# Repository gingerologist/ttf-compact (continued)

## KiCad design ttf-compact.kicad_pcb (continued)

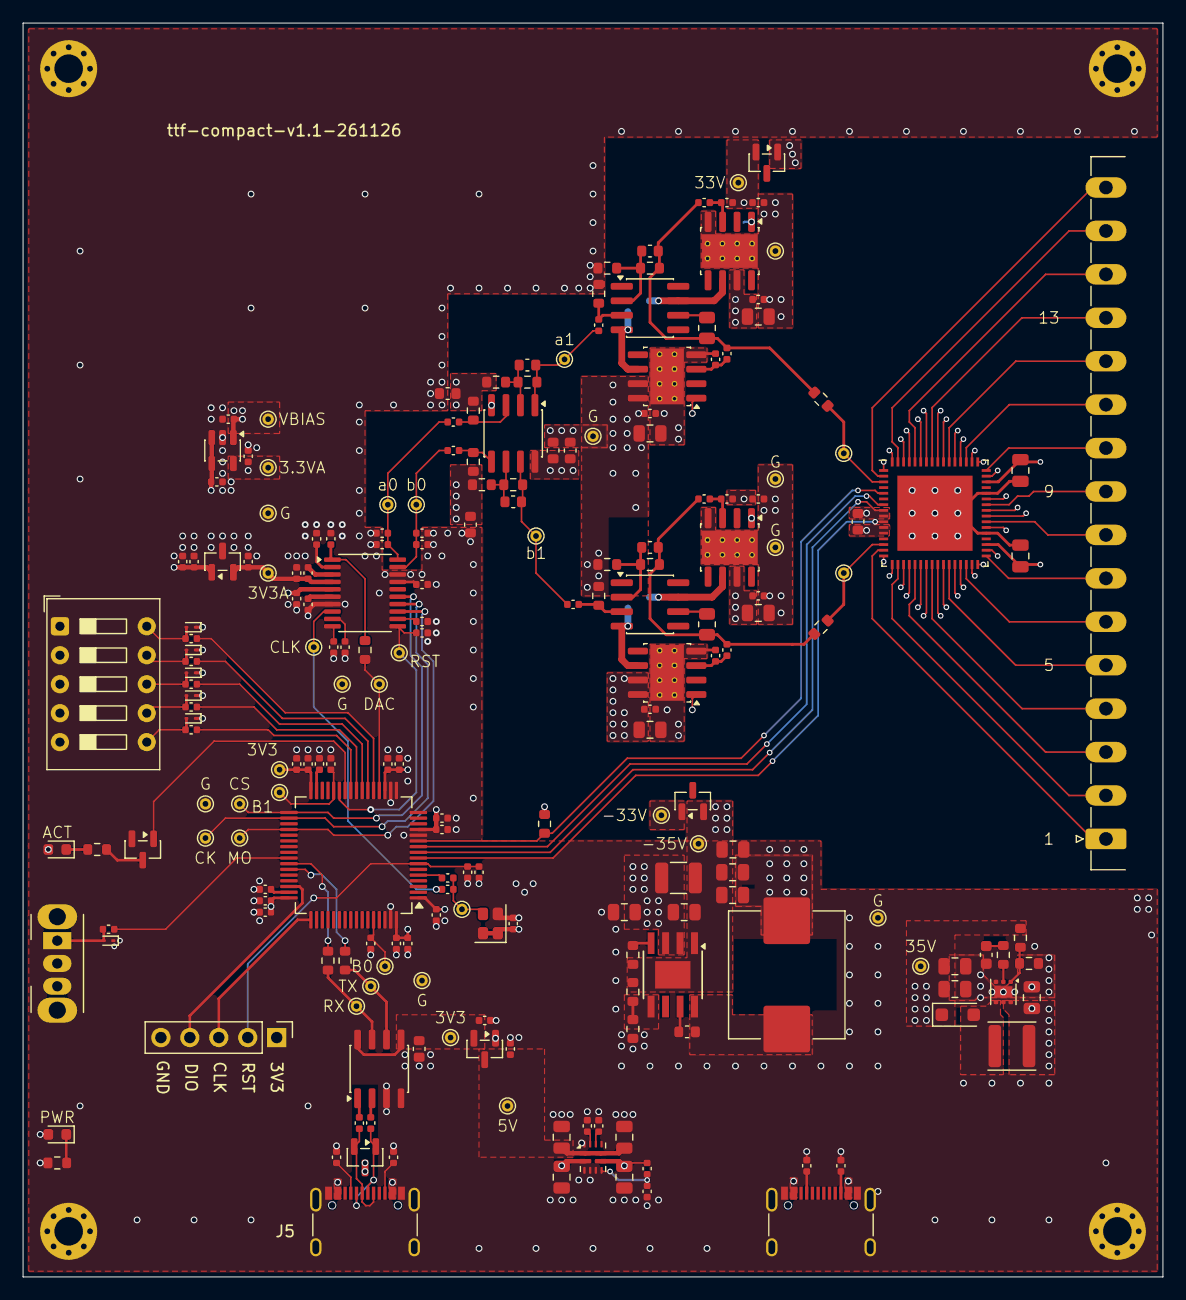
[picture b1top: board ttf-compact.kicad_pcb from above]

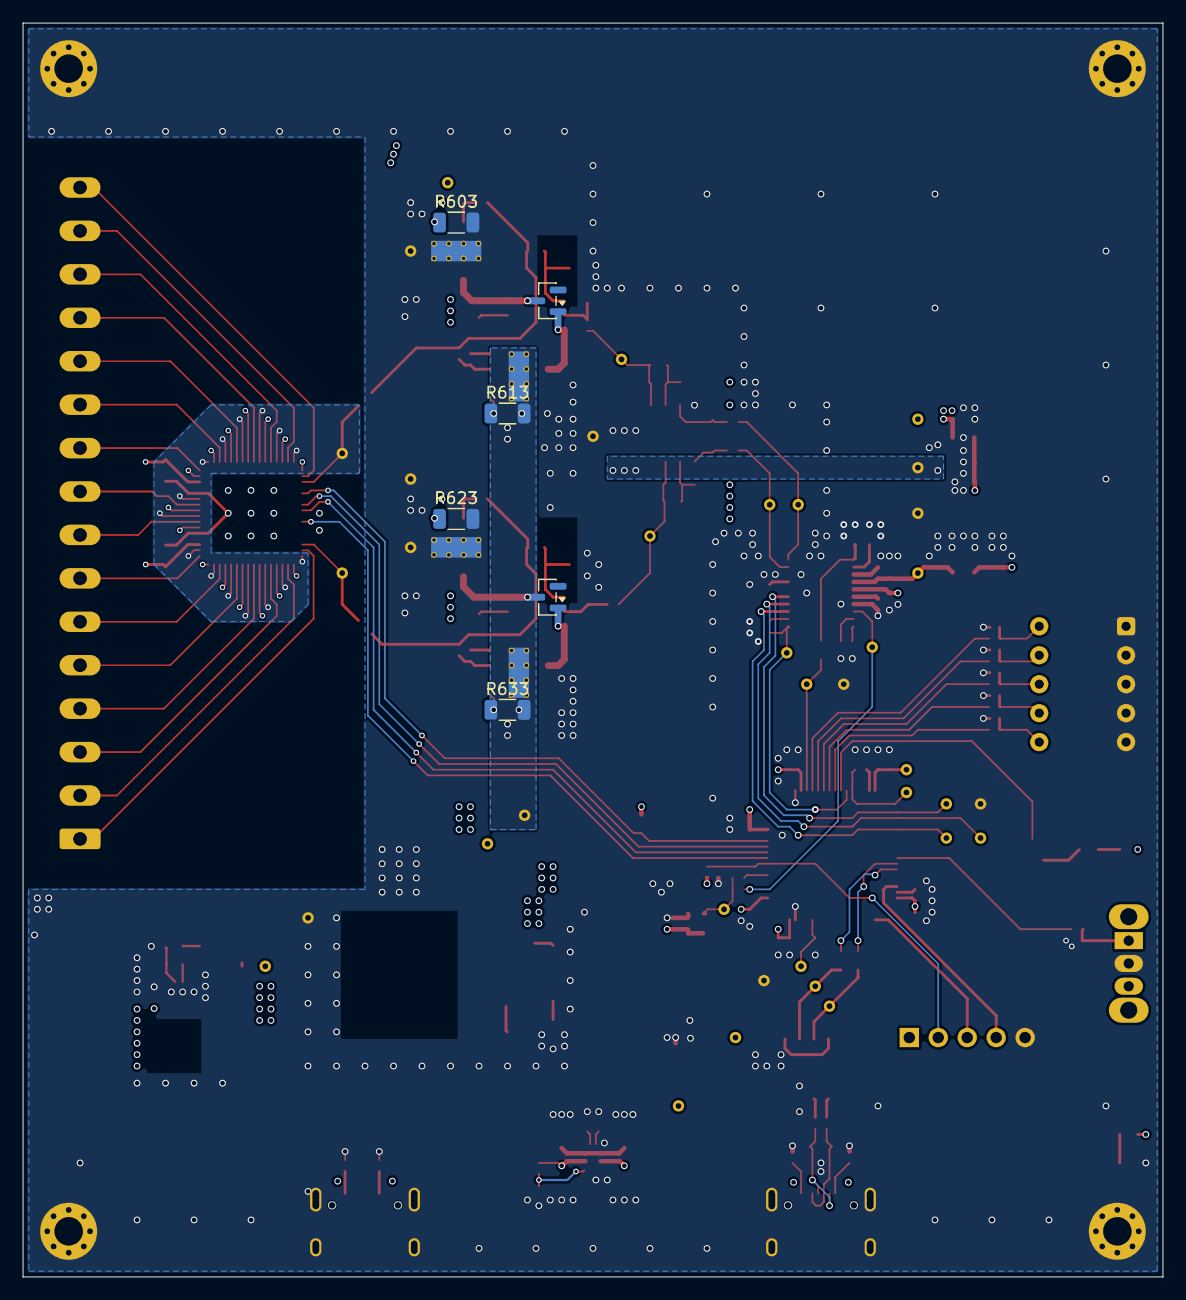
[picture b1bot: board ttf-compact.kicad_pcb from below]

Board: 4 copper layers, 100.0 x 110.0 mm, 221 parts (6 on the bottom side), 124 nets.

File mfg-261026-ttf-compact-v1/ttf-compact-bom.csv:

"Comment","Description","Designator","Footprint","Quantity","Supplier Part"
"1u,10%,25V","Unpolarized capacitor","C1,C15,C32,C33,C55,C650,C652,C660,C662,C985,C986,C987","0402","12","C52923"
"100n,10%,50V","Unpolarized capacitor","C2,C18,C602,C603,C612,C622,C623,C632","0402","8","C307331"
"10n,10%,50V","Unpolarized capacitor","C3,C4","0402","2","C15195"
"18p,±5%,50V","Unpolarized capacitor","C5,C10","0402","2","C1549"
"100n,10%,16V","Unpolarized capacitor","C6,C9,C11,C36,C37,C38,C50,C51,C52,C53,C54,C60","0402","12","C1525"
"2.2u,20%,6.3V","Unpolarized capacitor","C7,C8,C56,C57,C58,C59","0402","6","C12530"
"100n,10%,50V","Unpolarized capacitor","C31,C405,C667","0603","3","C14663"
"10u,10%,50V","Unpolarized capacitor","C301,C304,C400,C403,C404,C601,C611,C621,C631,C700,C701,C702,C703,C704","0805","14","C440198"
"15n,10%,50V","Unpolarized capacitor","C302","0603","1","C5137641"
"2.2u,10%,50V","Unpolarized capacitor","C303","0805","1","C377773"
"10u,10%,100V","10u, 100V Cap","C401","1210","1","C5156756"
"100n,10%,100V","Unpolarized capacitor","C402,C503,C504","0805","3","C28233"
"1u,10%,50V","Unpolarized capacitor","C501","0603","1","C15849"
"10p,5%,50V","Unpolarized capacitor","C651,C653,C661,C663","0603","4","C1634"
"2.2u,10%,16V","Unpolarized capacitor","C654,C664,C668","0603","3","C23630"
"GREEN","Green LED","D1,D7","0603","2","C84267"
"3.3V,15p","3.3V ESD","D2,D3,D4,D5,D6,D8","SOD-923","6","C96512"
"BAV99,215","Dual Switching Diode","D9,D10","SOT-23","2","C2500"
"100V,2A","100V 2A Schottky","D301","SOD-123FL","1","C511868"
"1x16P,3.81mm","Terminal Block","J1","RA,P=3.81mm","1","C127850"
"USB_C_U262-161N-4BVC11","USB-C 2.0 Receptacle","J5,J999","USBC20_16P","2","C319148"
"12uH,20%,1.7A","Inductor","L301","SMD,4x4mm","1","C96892"
"68uH,20%,3A","Power Inductor","L401","SMD,11x10mm","1","C408492"
"DTC143ZCA","Digital Transistor","Q1","SOT-23","1","C15236"
"10R,1%","Resistor","R1,R2","0603","2","C22859"
"10k,1%","Resistor","R4,R6,R7,R8,R10,R11,R18","0402","7","C25744"
"6.8k,1%","Resistor","R5","0603","1","C23212"
"33R,1%","Resistor","R9,R17","0402","2","C25105"
"220R,0.1%","Resistor","R13,R14","0402","2","C853134"
"22R,1%","Resistor","R31,R32","0402","2","C25092"
"5.1k,1%","Resistor","R33,R35,R998,R999","0402","4","C25905"
"0R,1%","Resistor","R36,R37","0603","2","C21189"
"100R,1%","Resistor","R40,R41,R42,R43,R44,R45","0402","6","C25076"
"10k,1%","Resistor","R93,R94,R403,R655,R665","0603","5","C25804"
"86.6k,1%","Resistor","R301","0603","1","C3000725"
"287k,1%","Resistor","R302","0603","1","C5159700"
"10.5k,1%","Resistor","R303","0603","1","C2933127"
"64.9k,1%","Resistor","R401","0603","1","C2960807"
"340k,1%","Resistor","R402","0603","1","C2933203"
"100k,1%","Resistor","R501","0603","1","C25803"
"33k,1%","Resistor","R601,R602,R611,R612,R621,R622,R631,R632","0402","8","C25779"
"953R,1%","Resistor","R651,R661","0603","2","C2933268"
"1k,1%","Resistor","R652,R662","0603","2","C21190"
"20k,1%","Resistor","R653,R663","0603","2","C4184"
"7.5k,1%","Resistor","R654,R664","0603","2","C23234"
"30k,1%","Resistor","R656,R666","0603","2","C22984"
"220R,1%","Resistor","R9650,R9660","0805","2","C294695"
"SW_DIP_x05","DIP Switch","SW1","THT","1","C129061"
"OS102011MA1QN1","SPDT Slider","SW999","THT","1","C226259"
"OPA2365AIDR","50MHz RRIO Dual Opamp","U1","SOIC-8","1","C130011"
"TI REF2033AIDDCR","3.3V/1.65V Dual-Output Voltage Reference","U2","SOT-23-5","1","C440747"
"STM32F405RGTx","STMicroelectronics Arm Cortex-M4 MCU, 1024KB flash, 192KB RAM, 168 MHz, 1.8-3.6V, 51 GPIO, LQFP64","U4","LQFP-64(10x10)","1","C15742"
"ESDA5V3L","ESD for USB DP/DM","U5","SOT-23-3","1","C587142"
"CH340N","USB serial converter","U6","SOP-8","1","C2977777"
"XC6206P332MR-G","200mA, 3.3V LDO","U7","SOT-23-3L","1","C5446"
"AD9834BRUZ","DDS","U11","TSSOP-20","1","C116589"
"REF3033","3.3V 50-ppm/°C Max, 50-μA, CMOS Voltage Reference, SOT-23-3","U13","SOT-23","1","C36658"
"TI TPS61170DRVR","Boost Converter","U302","WSON-6(2x2)","1","C15163"
"LMR38010SDDA","High voltage buck","U401","SOPowerPAD-8","1","C5219310"
"HV2801K6-G","High Voltage 16 Channel 2:1 Multiplexer","U501","QFN-64-EP(9x9)","1","C633457"
"BUF634AIDDA","high speed buffer","U601,U611,U621,U631","SOIC-8","4","C2864582"
"OPA892DR","opamp","U650,U660","SOIC-8","2","C22396184"
"CH213K","5V1A Ideal Diode","U700,U701,U702,U703","SOT-23-3","4","C5456874"
"25MHz, 50ppm, 1.6-3.6V","SG-210STF, CMOS Crystal Oscillator SPXO","Y1","SMD2520-4P","1","C70560"
